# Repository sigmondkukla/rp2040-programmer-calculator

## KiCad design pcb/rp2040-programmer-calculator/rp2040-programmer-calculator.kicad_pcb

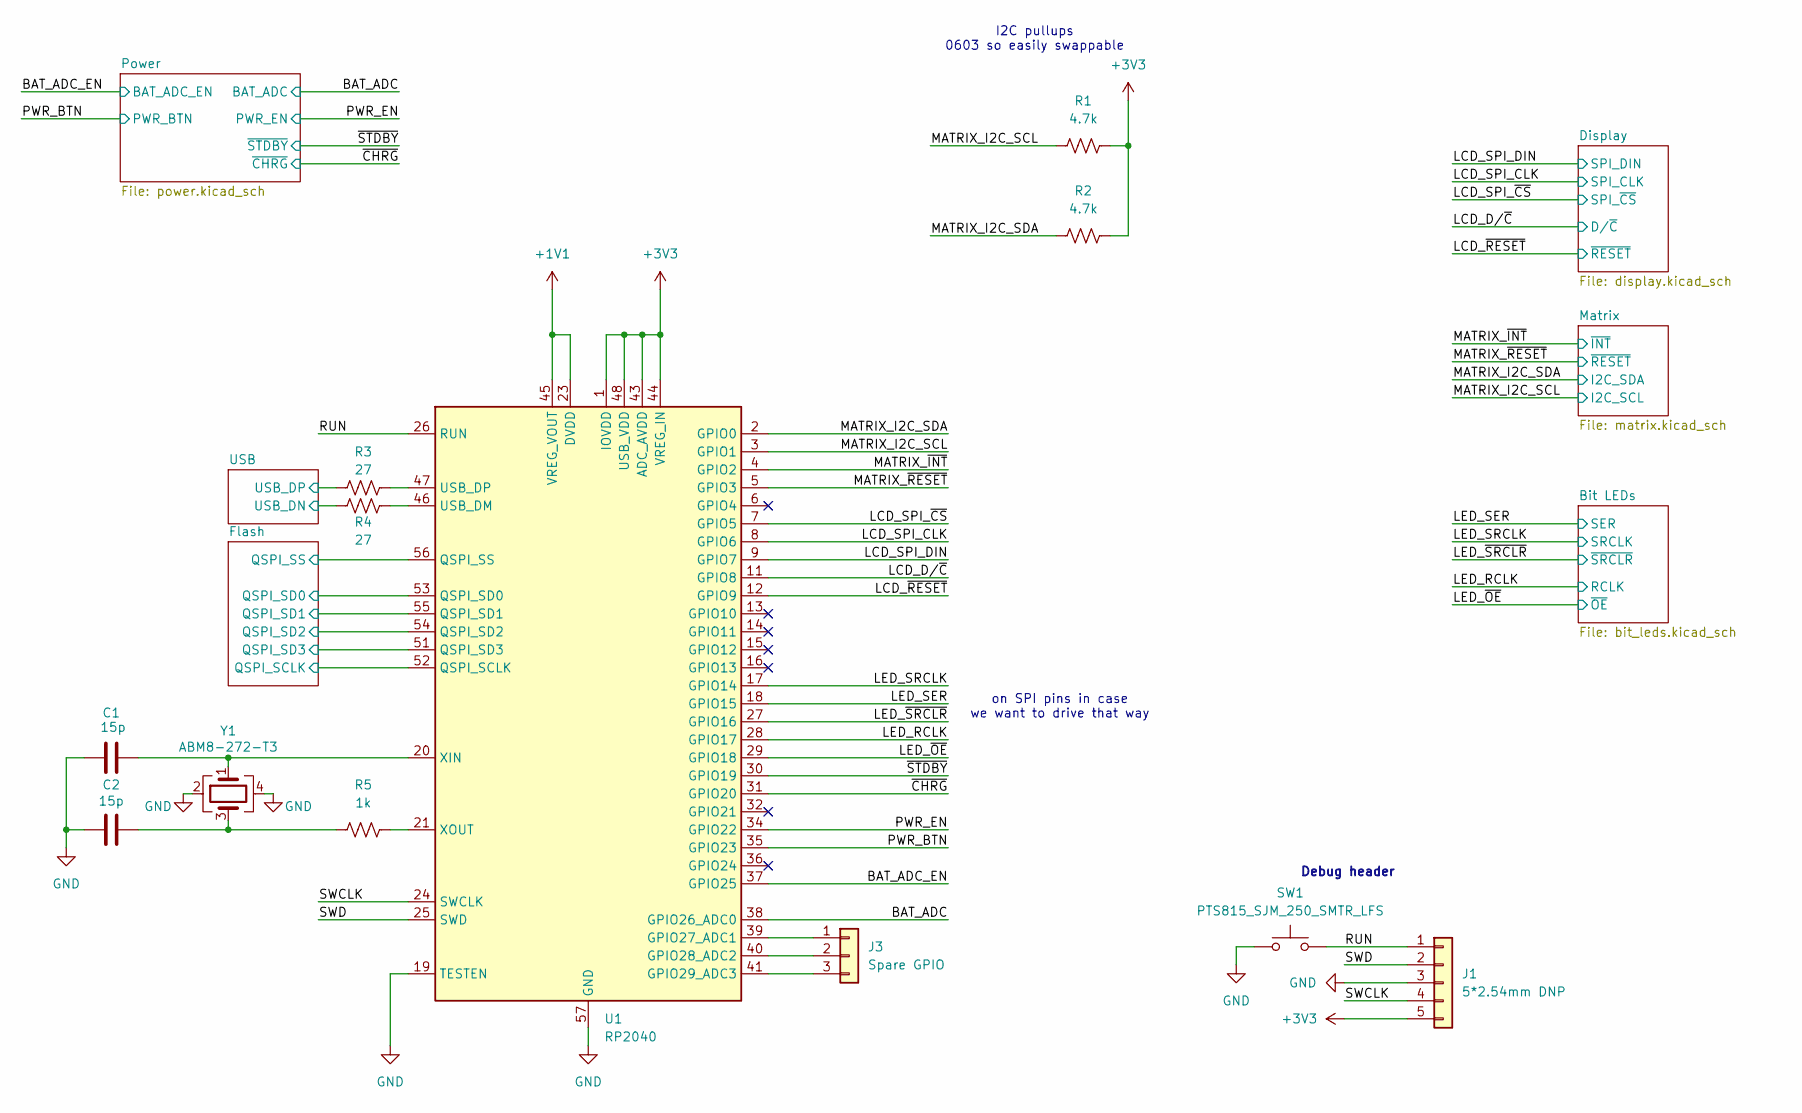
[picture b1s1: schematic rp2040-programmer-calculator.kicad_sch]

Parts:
C1, C2: 15p; C_0402_1005Metric; LCSC C1548
J1: 5*2.54mm DNP; PinHeader_1x05_P2.54mm_Vertical
J3: Spare GPIO; PinHeader_1x03_P2.00mm_Vertical
R1, R2: 4.7k; R_0603_1608Metric
R3, R4: 27; R_0402_1005Metric
R5: 1k; R_0402_1005Metric
SW1: PTS815_SJM_250_SMTR_LFS; SW_Push_PTS815_SJM_250_SMTR_LFS
U1: RP2040; QFN-56-1EP_7x7mm_P0.4mm_EP3.2x3.2mm
Y1: ABM8-272-T3; Crystal_SMD_Abracon_ABM8G-4Pin_3.2x2.5mm; LCSC C20625731

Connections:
+1V1: U1.23 (DVDD), U1.45 (VREG_VOUT), U1.50 (DVDD); also elsewhere on the board
+3V3: J1.5, R1.2, R2.2, U1.1 (IOVDD), U1.10 (IOVDD), U1.22 (IOVDD), U1.33 (IOVDD), U1.42 (IOVDD), U1.43 (ADC_AVDD), U1.44 (VREG_IN), U1.48 (USB_VDD), U1.49 (IOVDD); also elsewhere on the board
/BAT_ADC: U1.38 (GPIO26_ADC0); also elsewhere on the board
/BAT_ADC_EN: U1.37 (GPIO25); also elsewhere on the board
/Flash/QSPI_SCLK: U1.52 (QSPI_SCLK); also elsewhere on the board
/Flash/QSPI_SD0: U1.53 (QSPI_SD0); also elsewhere on the board
/Flash/QSPI_SD1: U1.55 (QSPI_SD1); also elsewhere on the board
/Flash/QSPI_SD2: U1.54 (QSPI_SD2); also elsewhere on the board
/Flash/QSPI_SD3: U1.51 (QSPI_SD3); also elsewhere on the board
/Flash/QSPI_SS: U1.56 (QSPI_SS); also elsewhere on the board
/LCD_D/~C: U1.11 (GPIO8); also elsewhere on the board
/LCD_SPI_CLK: U1.8 (GPIO6); also elsewhere on the board
/LCD_SPI_DIN: U1.9 (GPIO7); also elsewhere on the board
/LCD_SPI_~CS: U1.7 (GPIO5); also elsewhere on the board
/LCD_~RESET: U1.12 (GPIO9); also elsewhere on the board
/LED_RCLK: U1.28 (GPIO17); also elsewhere on the board
/LED_SER: U1.18 (GPIO15); also elsewhere on the board
/LED_SRCLK: U1.17 (GPIO14); also elsewhere on the board
/LED_~OE: U1.29 (GPIO18); also elsewhere on the board
/LED_~SRCLR: U1.27 (GPIO16); also elsewhere on the board
/MATRIX_I2C_SCL: R1.1, U1.3 (GPIO1); also elsewhere on the board
/MATRIX_I2C_SDA: R2.1, U1.2 (GPIO0); also elsewhere on the board
/MATRIX_~INT: U1.4 (GPIO2); also elsewhere on the board
/MATRIX_~RESET: U1.5 (GPIO3); also elsewhere on the board
/PWR_BTN: U1.35 (GPIO23); also elsewhere on the board
/PWR_EN: U1.34 (GPIO22); also elsewhere on the board
/RUN: J1.1, SW1.2, U1.26 (RUN)
/SWCLK: J1.4, U1.24 (SWCLK)
/SWD: J1.2, U1.25 (SWD)
/USB/USB_DN: R4.1; also elsewhere on the board
/USB/USB_DP: R3.1; also elsewhere on the board
/~CHRG: U1.31 (GPIO20); also elsewhere on the board
/~STDBY: U1.30 (GPIO19); also elsewhere on the board
GND: C1.1, C2.1, J1.3, SW1.1, U1.19 (TESTEN), U1.57 (GND), Y1.2, Y1.4; also elsewhere on the board
unnamed: C2.2, R5.1, Y1.3
unnamed: J3.1, U1.39 (GPIO27_ADC1)
unnamed: J3.2, U1.40 (GPIO28_ADC2)
unnamed: J3.3, U1.41 (GPIO29_ADC3)
unnamed: R4.2, U1.46 (USB_DM)
unnamed: R3.2, U1.47 (USB_DP)
unnamed: C1.2, U1.20 (XIN), Y1.1
unnamed: R5.2, U1.21 (XOUT)

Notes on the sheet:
I2C pullups 0603 so easily swappable
on SPI pins in case we want to drive that way
Debug header

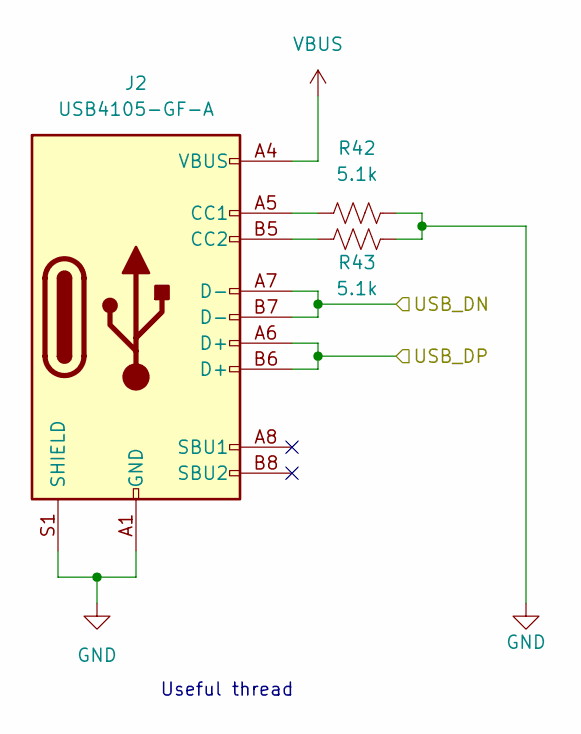
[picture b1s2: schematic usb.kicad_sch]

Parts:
J2: USB4105-GF-A; USB_C_Receptacle_GCT_USB4105-xx-A_16P_TopMnt_Horizontal
R42, R43: 5.1k; R_0603_1608Metric

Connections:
/USB/USB_DN: J2.A7 (D-), J2.B7 (D-); also elsewhere on the board
/USB/USB_DP: J2.A6 (D+), J2.B6 (D+); also elsewhere on the board
GND: J2.A1 (GND), J2.A12 (GND), J2.B1 (GND), J2.B12 (GND), J2.S1 (SHIELD), R42.2, R43.2; also elsewhere on the board
unnamed: J2.A5 (CC1), R42.1
unnamed: J2.B5 (CC2), R43.1
VBUS: J2.A4 (VBUS), J2.A9 (VBUS), J2.B4 (VBUS), J2.B9 (VBUS); also elsewhere on the board

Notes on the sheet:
Useful thread

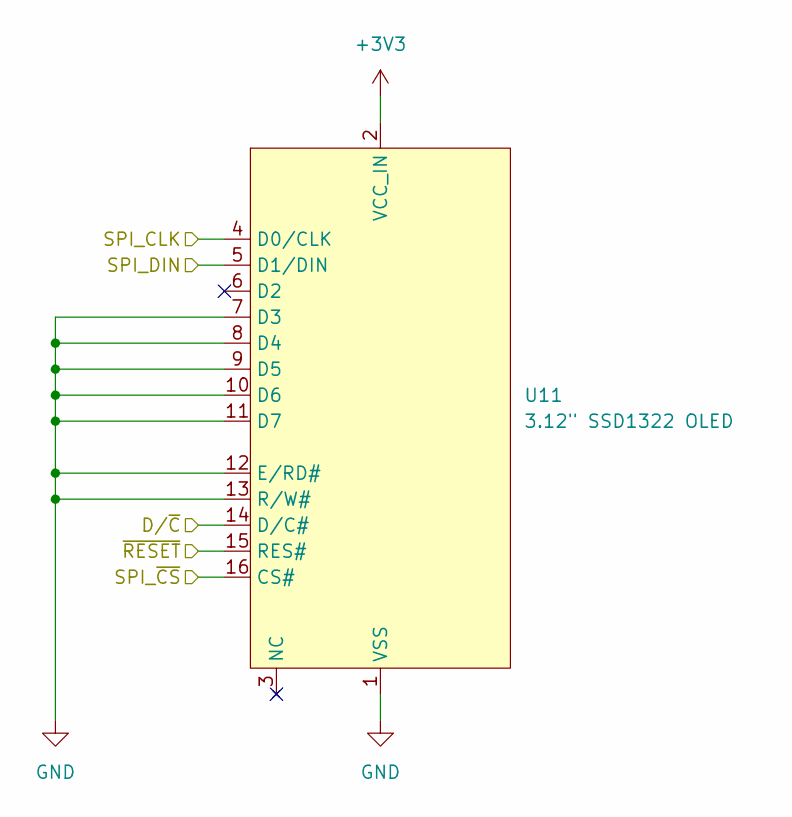
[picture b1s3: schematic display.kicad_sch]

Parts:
U11: 3.12" SSD1322 OLED; SSD1322_OLED

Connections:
+3V3: U11.2 (VCC_IN); also elsewhere on the board
/LCD_D/~C: U11.14 (D/C#); also elsewhere on the board
/LCD_SPI_CLK: U11.4 (D0/CLK); also elsewhere on the board
/LCD_SPI_DIN: U11.5 (D1/DIN); also elsewhere on the board
/LCD_SPI_~CS: U11.16 (CS#); also elsewhere on the board
/LCD_~RESET: U11.15 (RES#); also elsewhere on the board
GND: U11.1 (VSS), U11.7 (D3), U11.8 (D4), U11.9 (D5), U11.10 (D6), U11.11 (D7), U11.12 (E/RD#), U11.13 (R/W#); also elsewhere on the board

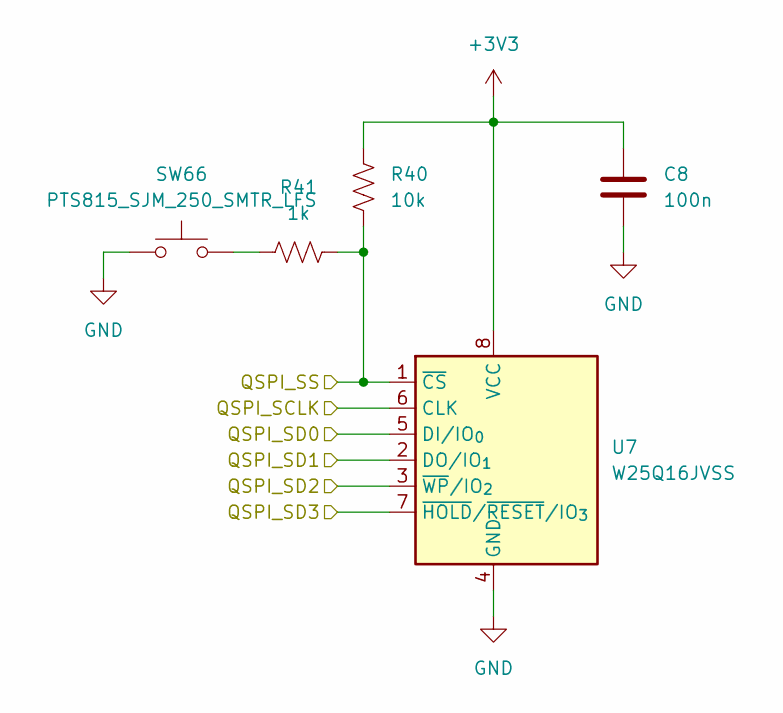
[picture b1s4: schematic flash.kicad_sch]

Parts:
C8: 100n; C_0603_1608Metric
R40: 10k; R_0603_1608Metric
R41: 1k; R_0603_1608Metric
SW66: PTS815_SJM_250_SMTR_LFS; SW_Push_PTS815_SJM_250_SMTR_LFS
U7: W25Q16JVSS; SOIC-8_5.3x5.3mm_P1.27mm

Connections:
+3V3: C8.1, R40.1, U7.8 (VCC); also elsewhere on the board
/Flash/QSPI_SCLK: U7.6 (CLK); also elsewhere on the board
/Flash/QSPI_SD0: U7.5 (DI/IO_{0}); also elsewhere on the board
/Flash/QSPI_SD1: U7.2 (DO/IO_{1}); also elsewhere on the board
/Flash/QSPI_SD2: U7.3 (~WP/IO_{2}); also elsewhere on the board
/Flash/QSPI_SD3: U7.7 (~HOLD/~RESET/IO_{3}); also elsewhere on the board
/Flash/QSPI_SS: R40.2, R41.2, U7.1 (~CS); also elsewhere on the board
GND: C8.2, SW66.1, U7.4 (GND); also elsewhere on the board
unnamed: R41.1, SW66.2

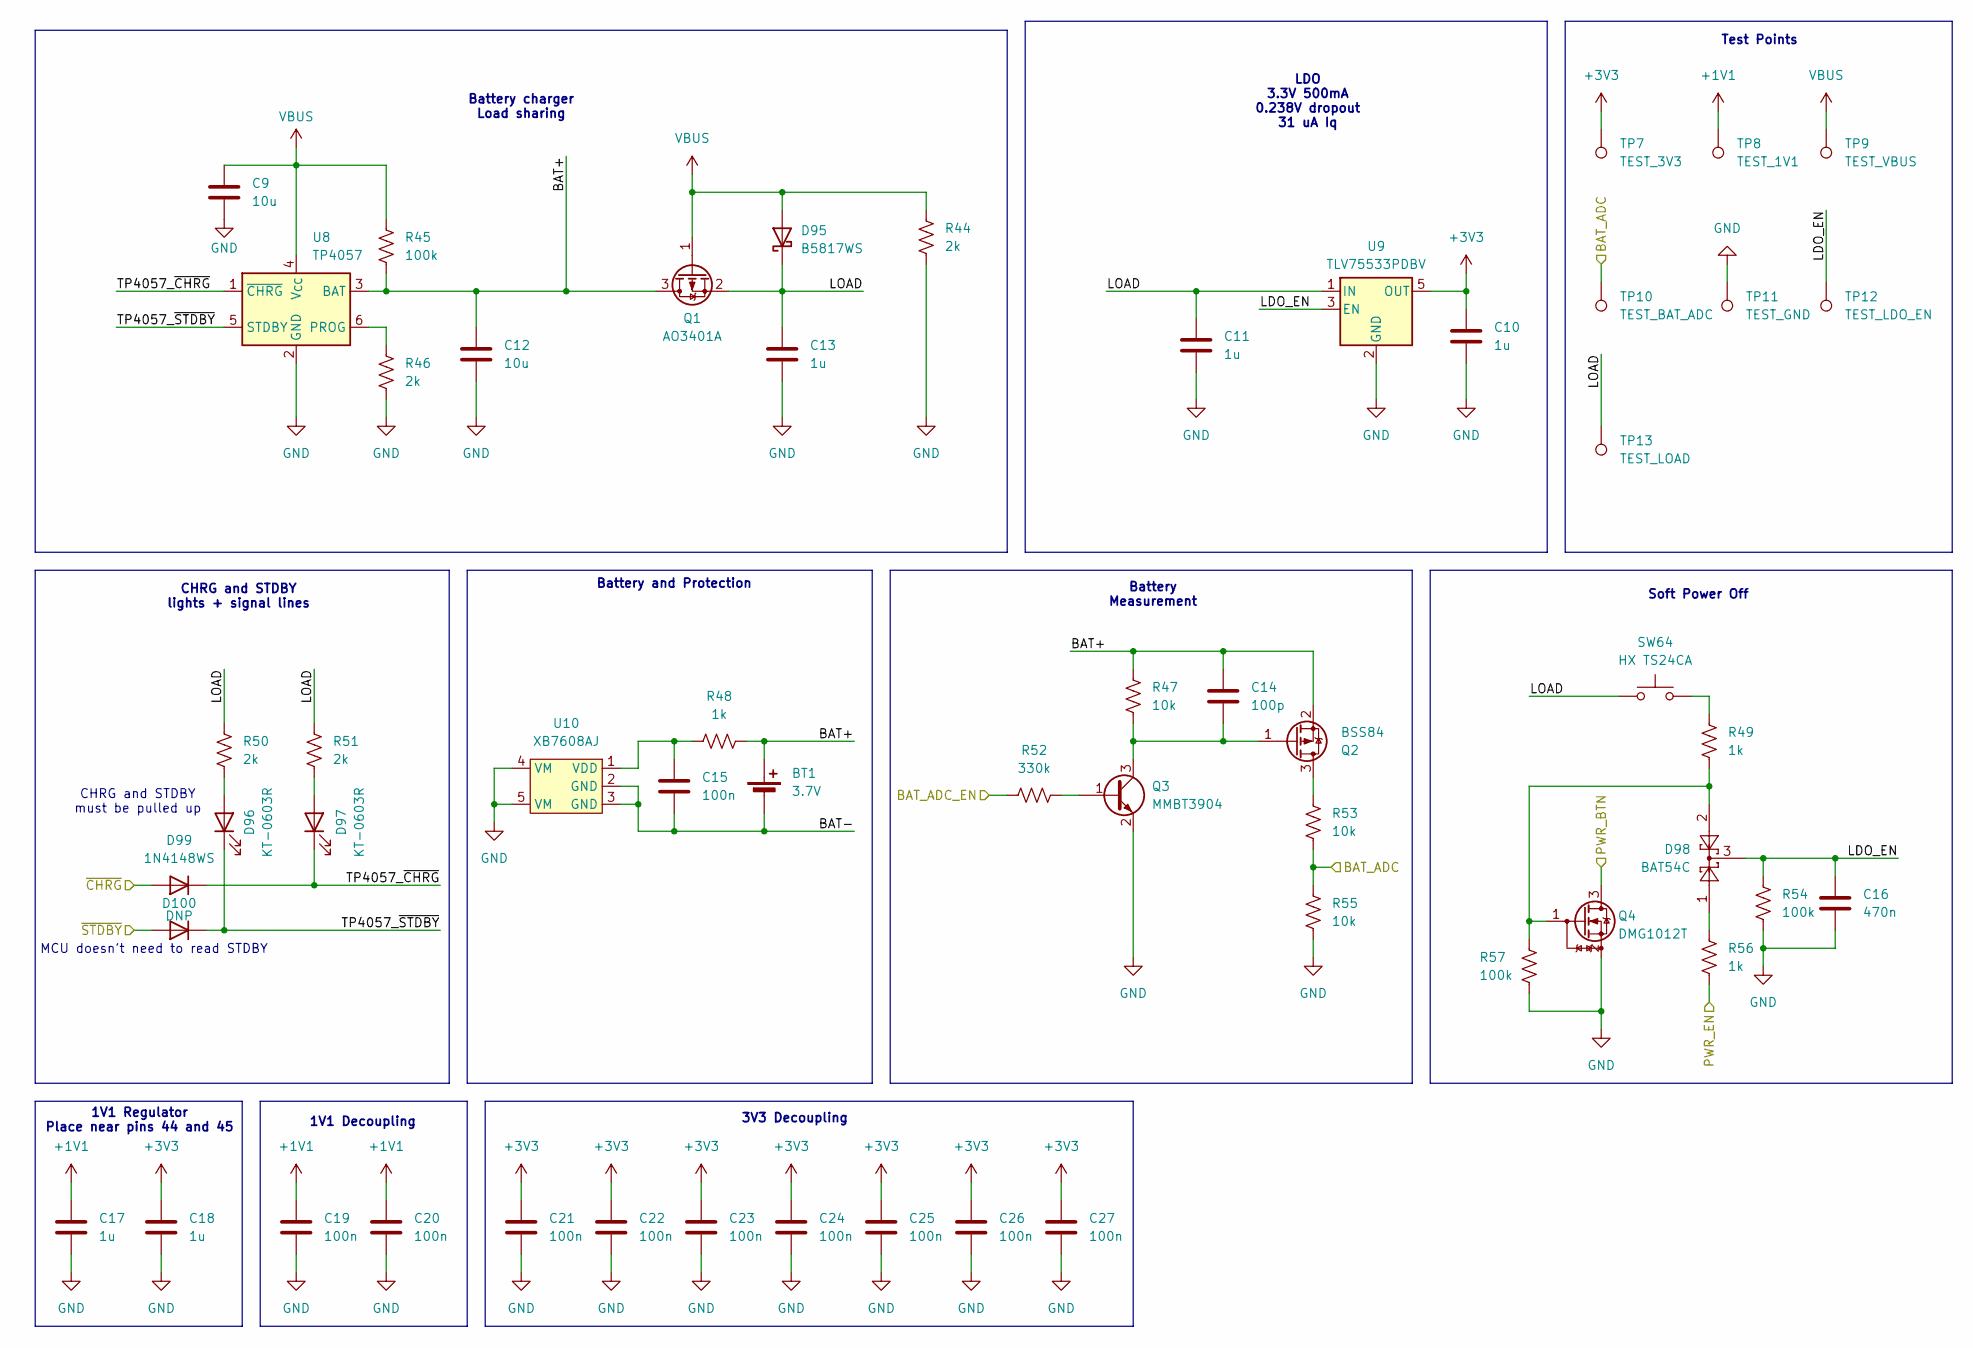
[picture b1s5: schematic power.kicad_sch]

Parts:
BT1: 3.7V; JST_PH_S2B-PH-K_1x02_P2.00mm_Horizontal
C9, C12: 10u; C_0603_1608Metric
C10, C11: 1u; C_0603_1608Metric; LCSC C52923
C13: 1u; C_0603_1608Metric
C14: 100p; C_0603_1608Metric
C15: 100n; C_0603_1608Metric
C16: 470n; C_0603_1608Metric
C17, C18: 1u; C_0402_1005Metric; LCSC C52923
C19, C20, C21, C22, C23, C24, C25, C26, C27: 100n; C_0402_1005Metric; LCSC C1525
D95: B5817WS; D_SOD-323
D96, D97: KT-0603R; LED_0603_1608Metric
D98: BAT54C; SOT-23-3
D99: 1N4148WS; D_SOD-323
D100: DNP; D_SOD-323
Q1: AO3401A; SOT-23-3
Q2: BSS84; SOT-23-3
Q3: MMBT3904; SOT-23
Q4: DMG1012T; SOT-523
R44, R46, R50, R51: 2k; R_0603_1608Metric
R45, R54, R57: 100k; R_0603_1608Metric
R47, R53, R55: 10k; R_0603_1608Metric
R48, R49, R56: 1k; R_0603_1608Metric
R52: 330k; R_0603_1608Metric
SW64: HX TS24CA; HX-TS24CA
TP7: TEST_3V3; TestPoint_Pad_D1.0mm
TP8: TEST_1V1; TestPoint_Pad_D1.0mm
TP9: TEST_VBUS; TestPoint_Pad_D1.0mm
TP10: TEST_BAT_ADC; TestPoint_Pad_D1.0mm
TP11: TEST_GND; TestPoint_Pad_D1.0mm
TP12: TEST_LDO_EN; TestPoint_Pad_D1.0mm
TP13: TEST_LOAD; TestPoint_Pad_D1.0mm
U8: TP4057; TSOT-23-6
U9: TLV75533PDBV; SOT-23-5
U10: XB7608AJ; CPC-5_L2.6-W2.6-P0.53-LS4.0-BL

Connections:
+1V1: C17.1, C19.1, C20.1, TP8.1; also elsewhere on the board
+3V3: C10.1, C18.1, C21.1, C22.1, C23.1, C24.1, C25.1, C26.1, C27.1, TP7.1, U9.5 (OUT); also elsewhere on the board
/BAT_ADC: R53.1, R55.2, TP10.1; also elsewhere on the board
/BAT_ADC_EN: R52.1; also elsewhere on the board
/PWR_BTN: Q4.3 (D); also elsewhere on the board
/PWR_EN: R56.2; also elsewhere on the board
/Power/BAT+: BT1.1 (+), C12.1, C14.1, Q1.3 (D), Q2.2 (S), R45.2, R47.2, R48.2, U8.3 (BAT)
/Power/BAT-: BT1.2 (-), C15.2, U10.2 (GND), U10.3 (GND)
/Power/LDO_EN: C16.1, D98.3, R54.1, TP12.1, U9.3 (EN)
/Power/LOAD: C11.1, C13.1, D95.1 (K), Q1.2 (S), R50.1, R51.1, SW64.2, TP13.1, U9.1 (IN)
/Power/TP4057_~CHRG: D97.1 (K), D99.1 (K), U8.1 (~CHRG)
/Power/TP4057_~STDBY: D96.1 (K), D100.1 (K), U8.5 (STDBY)
/~CHRG: D99.2 (A); also elsewhere on the board
/~STDBY: D100.2 (A); also elsewhere on the board
GND: C9.2, C10.2, C11.2, C12.2, C13.2, C16.2, C17.2, C18.2, C19.2, C20.2, C21.2, C22.2, C23.2, C24.2, C25.2, C26.2, C27.2, Q3.2 (E), Q4.2 (S), R44.2, R46.2, R54.2, R55.1, R57.2, TP11.1, U8.2 (GND), U9.2 (GND), U10.4 (VM), U10.5 (VM); also elsewhere on the board
unnamed: D96.2 (A), R50.2
unnamed: D97.2 (A), R51.2
unnamed: D98.1, R56.1
unnamed: Q2.3 (D), R53.2
unnamed: C14.2, Q2.1 (G), Q3.3 (C), R47.1
unnamed: Q3.1 (B), R52.2
unnamed: D98.2, Q4.1 (G), R49.2, R57.1
unnamed: R49.1, SW64.1
unnamed: R46.1, U8.6 (PROG)
unnamed: C15.1, R48.1, U10.1 (VDD)
VBUS: C9.1, D95.2 (A), Q1.1 (G), R44.1, R45.1, TP9.1, U8.4 (V_{CC}); also elsewhere on the board

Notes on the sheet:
MCU doesn't need to read STDBY
Battery Measurement
CHRG and STDBY lights + signal lines
CHRG and STDBY must be pulled up
LDO 3.3V 500mA 0.238V dropout 31 uA Iq
Test Points
3V3 Decoupling
Battery charger Load sharing
Soft Power Off
Battery and Protection
1V1 Regulator Place near pins 44 and 45
1V1 Decoupling

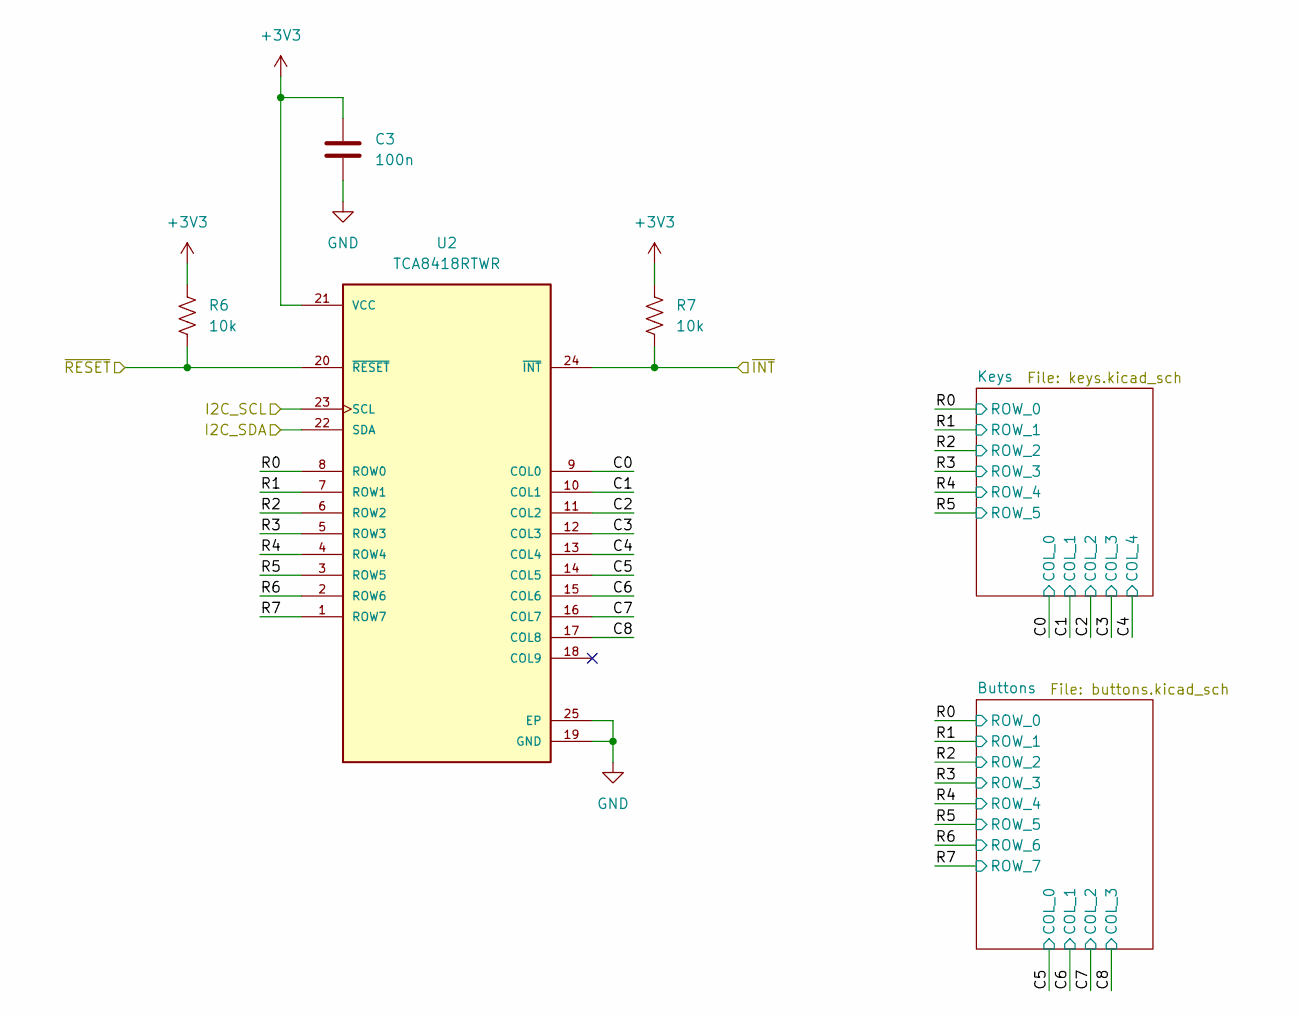
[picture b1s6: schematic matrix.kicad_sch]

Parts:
C3: 100n; C_0603_1608Metric
R6, R7: 10k; R_0603_1608Metric
U2: TCA8418RTWR; QFN50P400X400X80-25N; PARTREV G

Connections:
+3V3: C3.1, R6.1, R7.1, U2.21 (VCC); also elsewhere on the board
/MATRIX_I2C_SCL: U2.23 (SCL); also elsewhere on the board
/MATRIX_I2C_SDA: U2.22 (SDA); also elsewhere on the board
/MATRIX_~INT: R7.2, U2.24 (~INT); also elsewhere on the board
/MATRIX_~RESET: R6.2, U2.20 (~RESET); also elsewhere on the board
/Matrix/C0: U2.9 (COL0); also elsewhere on the board
/Matrix/C1: U2.10 (COL1); also elsewhere on the board
/Matrix/C2: U2.11 (COL2); also elsewhere on the board
/Matrix/C3: U2.12 (COL3); also elsewhere on the board
/Matrix/C4: U2.13 (COL4); also elsewhere on the board
/Matrix/C5: U2.14 (COL5); also elsewhere on the board
/Matrix/C6: U2.15 (COL6); also elsewhere on the board
/Matrix/C7: U2.16 (COL7); also elsewhere on the board
/Matrix/C8: U2.17 (COL8); also elsewhere on the board
/Matrix/R0: U2.8 (ROW0); also elsewhere on the board
/Matrix/R1: U2.7 (ROW1); also elsewhere on the board
/Matrix/R2: U2.6 (ROW2); also elsewhere on the board
/Matrix/R3: U2.5 (ROW3); also elsewhere on the board
/Matrix/R4: U2.4 (ROW4); also elsewhere on the board
/Matrix/R5: U2.3 (ROW5); also elsewhere on the board
/Matrix/R6: U2.2 (ROW6); also elsewhere on the board
/Matrix/R7: U2.1 (ROW7); also elsewhere on the board
GND: C3.2, U2.19 (GND), U2.25 (EP); also elsewhere on the board

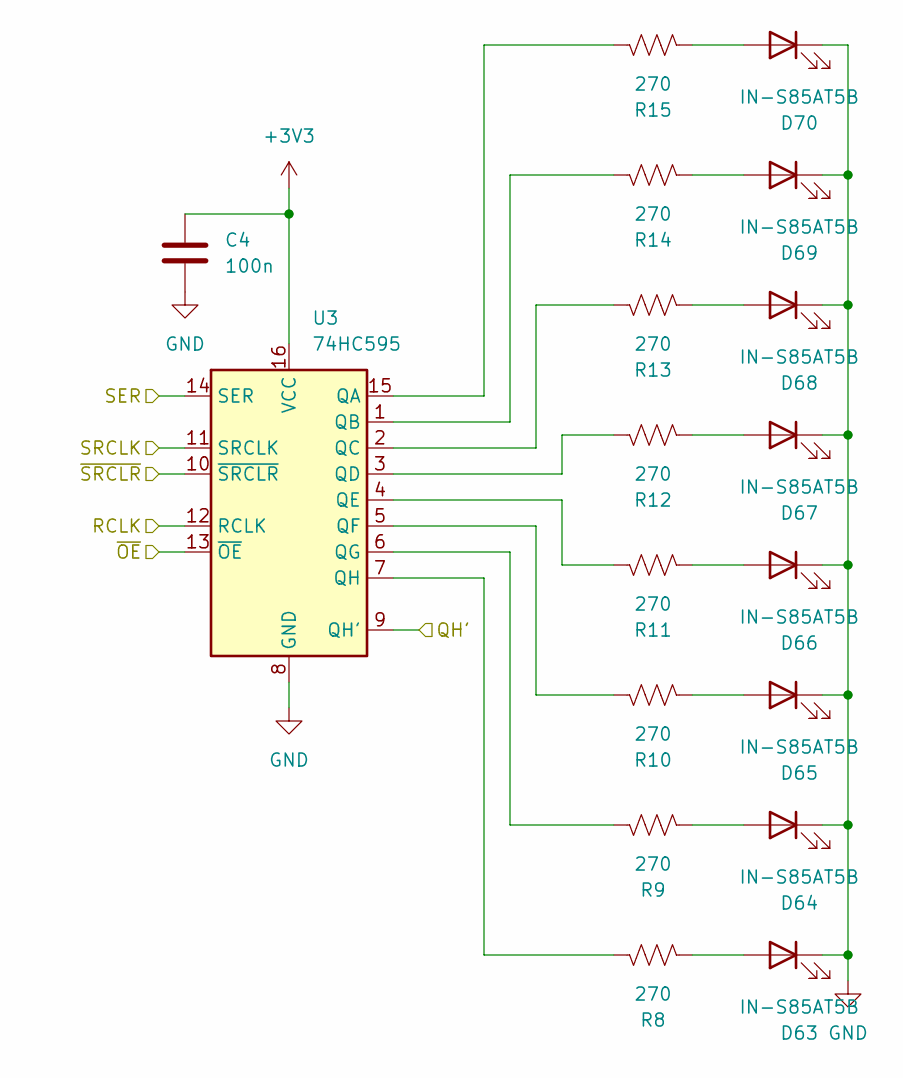
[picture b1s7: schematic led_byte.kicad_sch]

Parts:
C4: 100n; C_0603_1608Metric
D63, D64, D65, D66, D67, D68, D69, D70: IN-S85AT5B; LED_0805_2012Metric_Pad1.15x1.40mm_HandSolder
R8, R9, R10, R11, R12, R13, R14, R15: 270; R_0603_1608Metric_Pad0.98x0.95mm_HandSolder
U3: 74HC595; SOIC-16_3.9x9.9mm_P1.27mm

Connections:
+3V3: C4.1, U3.16 (VCC); also elsewhere on the board
/Bit LEDs/BYTE_0_OUT: U3.9 (QH'); also elsewhere on the board
/LED_RCLK: U3.12 (RCLK); also elsewhere on the board
/LED_SER: U3.14 (SER); also elsewhere on the board
/LED_SRCLK: U3.11 (SRCLK); also elsewhere on the board
/LED_~OE: U3.13 (~OE); also elsewhere on the board
/LED_~SRCLR: U3.10 (~SRCLR); also elsewhere on the board
GND: C4.2, D63.1 (K), D64.1 (K), D65.1 (K), D66.1 (K), D67.1 (K), D68.1 (K), D69.1 (K), D70.1 (K), U3.8 (GND); also elsewhere on the board
unnamed: D63.2 (A), R8.2
unnamed: D64.2 (A), R9.2
unnamed: D65.2 (A), R10.2
unnamed: D66.2 (A), R11.2
unnamed: D67.2 (A), R12.2
unnamed: D68.2 (A), R13.2
unnamed: D69.2 (A), R14.2
unnamed: D70.2 (A), R15.2
unnamed: R15.1, U3.15 (QA)
unnamed: R14.1, U3.1 (QB)
unnamed: R13.1, U3.2 (QC)
unnamed: R12.1, U3.3 (QD)
unnamed: R11.1, U3.4 (QE)
unnamed: R10.1, U3.5 (QF)
unnamed: R9.1, U3.6 (QG)
unnamed: R8.1, U3.7 (QH)

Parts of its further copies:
C5, C6, C7: 100n; C_0603_1608Metric
D71, D72, D73, D74, D75, D76, D77, D78, D79, D80, D81, D82, D83, D84, D85, D86, D87, D88, D89, D90, D91, D92, D93, D94: IN-S85AT5B; LED_0805_2012Metric_Pad1.15x1.40mm_HandSolder
R16, R17, R18, R19, R20, R21, R22, R23, R24, R25, R26, R27, R28, R29, R30, R31, R32, R33, R34, R35, R36, R37, R38, R39: 270; R_0603_1608Metric_Pad0.98x0.95mm_HandSolder
U4, U5, U6: 74HC595; SOIC-16_3.9x9.9mm_P1.27mm

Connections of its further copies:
+3V3: C5.1, C6.1, C7.1, U4.16 (VCC), U5.16 (VCC), U6.16 (VCC); also elsewhere on the board
/Bit LEDs/BYTE_0_OUT: U4.14 (SER); also elsewhere on the board
/Bit LEDs/BYTE_1_OUT: U4.9 (QH'), U5.14 (SER)
/Bit LEDs/BYTE_2_OUT: U5.9 (QH'), U6.14 (SER)
/Bit LEDs/LED_Byte_3/QH&apos;: U6.9 (QH')
/LED_RCLK: U4.12 (RCLK), U5.12 (RCLK), U6.12 (RCLK); also elsewhere on the board
/LED_SRCLK: U4.11 (SRCLK), U5.11 (SRCLK), U6.11 (SRCLK); also elsewhere on the board
/LED_~OE: U4.13 (~OE), U5.13 (~OE), U6.13 (~OE); also elsewhere on the board
/LED_~SRCLR: U4.10 (~SRCLR), U5.10 (~SRCLR), U6.10 (~SRCLR); also elsewhere on the board
GND: C5.2, C6.2, C7.2, D71.1 (K), D72.1 (K), D73.1 (K), D74.1 (K), D75.1 (K), D76.1 (K), D77.1 (K), D78.1 (K), D79.1 (K), D80.1 (K), D81.1 (K), D82.1 (K), D83.1 (K), D84.1 (K), D85.1 (K), D86.1 (K), D87.1 (K), D88.1 (K), D89.1 (K), D90.1 (K), D91.1 (K), D92.1 (K), D93.1 (K), D94.1 (K), U4.8 (GND), U5.8 (GND), U6.8 (GND); also elsewhere on the board
unnamed: D71.2 (A), R16.2
unnamed: D72.2 (A), R17.2
unnamed: D73.2 (A), R18.2
unnamed: D74.2 (A), R19.2
unnamed: D75.2 (A), R20.2
unnamed: D76.2 (A), R21.2
unnamed: D77.2 (A), R22.2
unnamed: D78.2 (A), R23.2
unnamed: D79.2 (A), R24.2
unnamed: D80.2 (A), R25.2
unnamed: D81.2 (A), R26.2
unnamed: D82.2 (A), R27.2
unnamed: D83.2 (A), R28.2
unnamed: D84.2 (A), R29.2
unnamed: D85.2 (A), R30.2
unnamed: D86.2 (A), R31.2
unnamed: D87.2 (A), R32.2
unnamed: D88.2 (A), R33.2
unnamed: D89.2 (A), R34.2
unnamed: D90.2 (A), R35.2
unnamed: D91.2 (A), R36.2
unnamed: D92.2 (A), R37.2
unnamed: D93.2 (A), R38.2
unnamed: D94.2 (A), R39.2
unnamed: R23.1, U4.15 (QA)
unnamed: R22.1, U4.1 (QB)
unnamed: R21.1, U4.2 (QC)
unnamed: R20.1, U4.3 (QD)
unnamed: R19.1, U4.4 (QE)
unnamed: R18.1, U4.5 (QF)
unnamed: R17.1, U4.6 (QG)
unnamed: R16.1, U4.7 (QH)
unnamed: R31.1, U5.15 (QA)
unnamed: R30.1, U5.1 (QB)
unnamed: R29.1, U5.2 (QC)
unnamed: R28.1, U5.3 (QD)
unnamed: R27.1, U5.4 (QE)
unnamed: R26.1, U5.5 (QF)
unnamed: R25.1, U5.6 (QG)
unnamed: R24.1, U5.7 (QH)
unnamed: R39.1, U6.15 (QA)
unnamed: R38.1, U6.1 (QB)
unnamed: R37.1, U6.2 (QC)
unnamed: R36.1, U6.3 (QD)
unnamed: R35.1, U6.4 (QE)
unnamed: R34.1, U6.5 (QF)
unnamed: R33.1, U6.6 (QG)
unnamed: R32.1, U6.7 (QH)

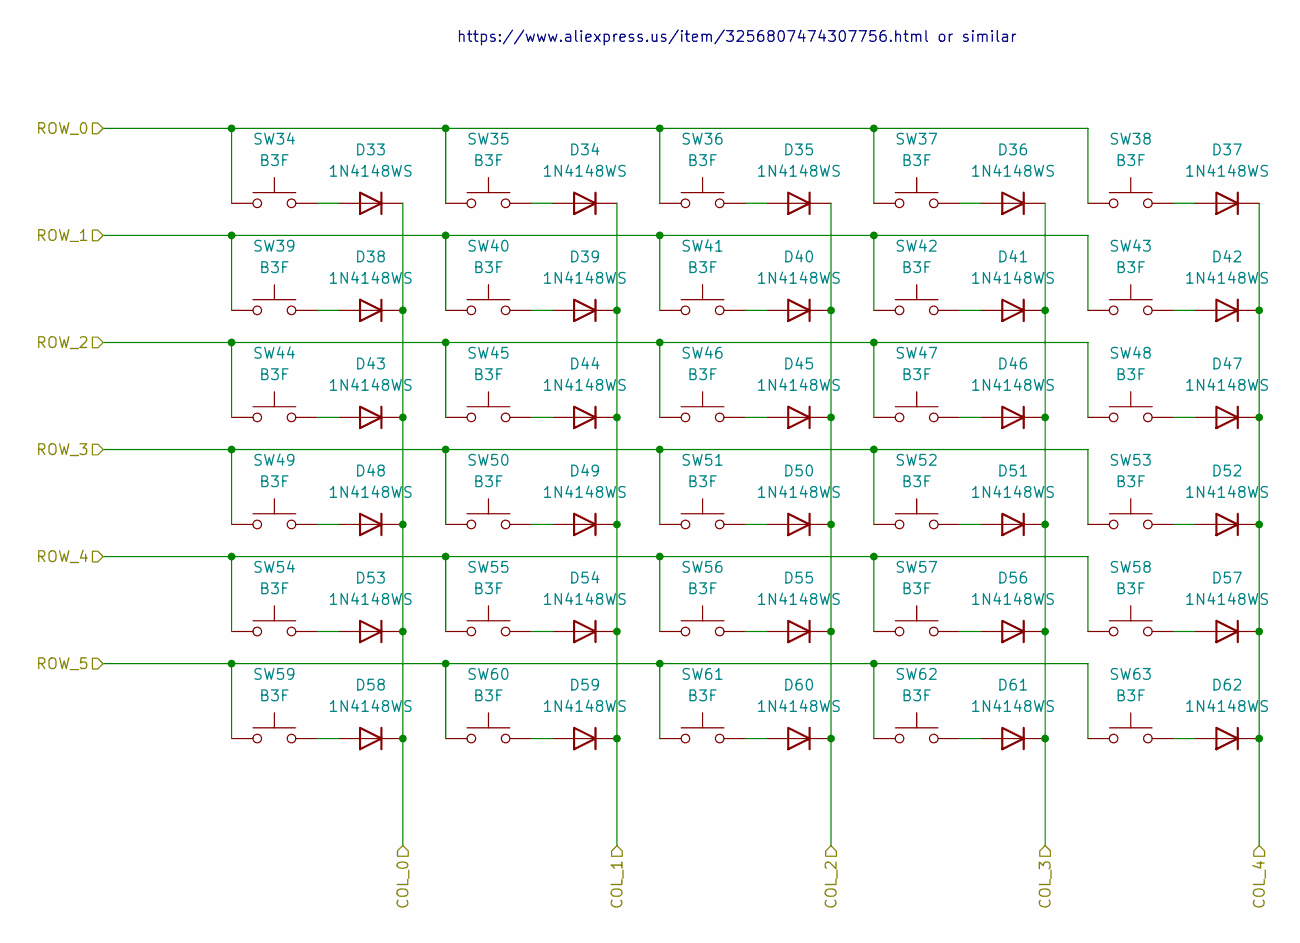
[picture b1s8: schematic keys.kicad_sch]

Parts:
D33, D34, D35, D36, D37, D38, D39, D40, D41, D42, D43, D44, D45, D46, D47, D48, D49, D50, D51, D52, D53, D54, D55, D56, D57, D58, D59, D60, D61, D62: 1N4148WS; D_SOD-323
SW34, SW35, SW36, SW37, SW38, SW39, SW40, SW41, SW42, SW43, SW44, SW45, SW46, SW47, SW48, SW49, SW50, SW51, SW52, SW53, SW54, SW55, SW56, SW57, SW58, SW59, SW60, SW61, SW62, SW63: B3F; SW_SPST_Omron_B3F-40xx

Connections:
/Matrix/C0: D33.1 (K), D38.1 (K), D43.1 (K), D48.1 (K), D53.1 (K), D58.1 (K); also elsewhere on the board
/Matrix/C1: D34.1 (K), D39.1 (K), D44.1 (K), D49.1 (K), D54.1 (K), D59.1 (K); also elsewhere on the board
/Matrix/C2: D35.1 (K), D40.1 (K), D45.1 (K), D50.1 (K), D55.1 (K), D60.1 (K); also elsewhere on the board
/Matrix/C3: D36.1 (K), D41.1 (K), D46.1 (K), D51.1 (K), D56.1 (K), D61.1 (K); also elsewhere on the board
/Matrix/C4: D37.1 (K), D42.1 (K), D47.1 (K), D52.1 (K), D57.1 (K), D62.1 (K); also elsewhere on the board
/Matrix/R0: SW34.1, SW35.1, SW36.1, SW37.1, SW38.1; also elsewhere on the board
/Matrix/R1: SW39.1, SW40.1, SW41.1, SW42.1, SW43.1; also elsewhere on the board
/Matrix/R2: SW44.1, SW45.1, SW46.1, SW47.1, SW48.1; also elsewhere on the board
/Matrix/R3: SW49.1, SW50.1, SW51.1, SW52.1, SW53.1; also elsewhere on the board
/Matrix/R4: SW54.1, SW55.1, SW56.1, SW57.1, SW58.1; also elsewhere on the board
/Matrix/R5: SW59.1, SW60.1, SW61.1, SW62.1, SW63.1; also elsewhere on the board
unnamed: D33.2 (A), SW34.2
unnamed: D34.2 (A), SW35.2
unnamed: D35.2 (A), SW36.2
unnamed: D36.2 (A), SW37.2
unnamed: D37.2 (A), SW38.2
unnamed: D38.2 (A), SW39.2
unnamed: D39.2 (A), SW40.2
unnamed: D40.2 (A), SW41.2
unnamed: D41.2 (A), SW42.2
unnamed: D42.2 (A), SW43.2
unnamed: D43.2 (A), SW44.2
unnamed: D44.2 (A), SW45.2
unnamed: D45.2 (A), SW46.2
unnamed: D46.2 (A), SW47.2
unnamed: D47.2 (A), SW48.2
unnamed: D48.2 (A), SW49.2
unnamed: D49.2 (A), SW50.2
unnamed: D50.2 (A), SW51.2
unnamed: D51.2 (A), SW52.2
unnamed: D52.2 (A), SW53.2
unnamed: D53.2 (A), SW54.2
unnamed: D54.2 (A), SW55.2
unnamed: D55.2 (A), SW56.2
unnamed: D56.2 (A), SW57.2
unnamed: D57.2 (A), SW58.2
unnamed: D58.2 (A), SW59.2
unnamed: D59.2 (A), SW60.2
unnamed: D60.2 (A), SW61.2
unnamed: D61.2 (A), SW62.2
unnamed: D62.2 (A), SW63.2

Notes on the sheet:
https://www.aliexpress.us/item/3256807474307756.html or similar

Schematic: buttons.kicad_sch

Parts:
D1, D2, D3, D4, D5, D6, D7, D8, D9, D10, D11, D12, D13, D14, D15, D16, D17, D18, D19, D20, D21, D22, D23, D24, D25, D26, D27, D28, D29, D30, D31, D32: 1N4148WS; D_SOD-323
SW2, SW3, SW4, SW5, SW6, SW7, SW8, SW9, SW10, SW11, SW12, SW13, SW14, SW15, SW16, SW17, SW18, SW19, SW20, SW21, SW22, SW23, SW24, SW25, SW26, SW27, SW28, SW29, SW30, SW31, SW32, SW33: PTS636SL50 LFS; PTS636SL50LFS

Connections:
/Matrix/C5: D1.1 (K), D2.1 (K), D3.1 (K), D4.1 (K), D5.1 (K), D6.1 (K), D7.1 (K), D8.1 (K); also elsewhere on the board
/Matrix/C6: D9.1 (K), D10.1 (K), D11.1 (K), D12.1 (K), D13.1 (K), D14.1 (K), D15.1 (K), D16.1 (K); also elsewhere on the board
/Matrix/C7: D17.1 (K), D18.1 (K), D19.1 (K), D20.1 (K), D21.1 (K), D22.1 (K), D23.1 (K), D24.1 (K); also elsewhere on the board
/Matrix/C8: D25.1 (K), D26.1 (K), D27.1 (K), D28.1 (K), D29.1 (K), D30.1 (K), D31.1 (K), D32.1 (K); also elsewhere on the board
/Matrix/R0: SW2.1, SW10.1, SW18.1, SW26.1; also elsewhere on the board
/Matrix/R1: SW3.1, SW11.1, SW19.1, SW27.1; also elsewhere on the board
/Matrix/R2: SW4.1, SW12.1, SW20.1, SW28.1; also elsewhere on the board
/Matrix/R3: SW5.1, SW13.1, SW21.1, SW29.1; also elsewhere on the board
/Matrix/R4: SW6.1, SW14.1, SW22.1, SW30.1; also elsewhere on the board
/Matrix/R5: SW7.1, SW15.1, SW23.1, SW31.1; also elsewhere on the board
/Matrix/R6: SW8.1, SW16.1, SW24.1, SW32.1; also elsewhere on the board
/Matrix/R7: SW9.1, SW17.1, SW25.1, SW33.1; also elsewhere on the board
unnamed: D1.2 (A), SW2.2
unnamed: D2.2 (A), SW3.2
unnamed: D3.2 (A), SW4.2
unnamed: D4.2 (A), SW5.2
unnamed: D5.2 (A), SW6.2
unnamed: D6.2 (A), SW7.2
unnamed: D7.2 (A), SW8.2
unnamed: D8.2 (A), SW9.2
unnamed: D9.2 (A), SW10.2
unnamed: D10.2 (A), SW11.2
unnamed: D11.2 (A), SW12.2
unnamed: D12.2 (A), SW13.2
unnamed: D13.2 (A), SW14.2
unnamed: D14.2 (A), SW15.2
unnamed: D15.2 (A), SW16.2
unnamed: D16.2 (A), SW17.2
unnamed: D17.2 (A), SW18.2
unnamed: D18.2 (A), SW19.2
unnamed: D19.2 (A), SW20.2
unnamed: D20.2 (A), SW21.2
unnamed: D21.2 (A), SW22.2
unnamed: D22.2 (A), SW23.2
unnamed: D23.2 (A), SW24.2
unnamed: D24.2 (A), SW25.2
unnamed: D25.2 (A), SW26.2
unnamed: D26.2 (A), SW27.2
unnamed: D27.2 (A), SW28.2
unnamed: D28.2 (A), SW29.2
unnamed: D29.2 (A), SW30.2
unnamed: D30.2 (A), SW31.2
unnamed: D31.2 (A), SW32.2
unnamed: D32.2 (A), SW33.2

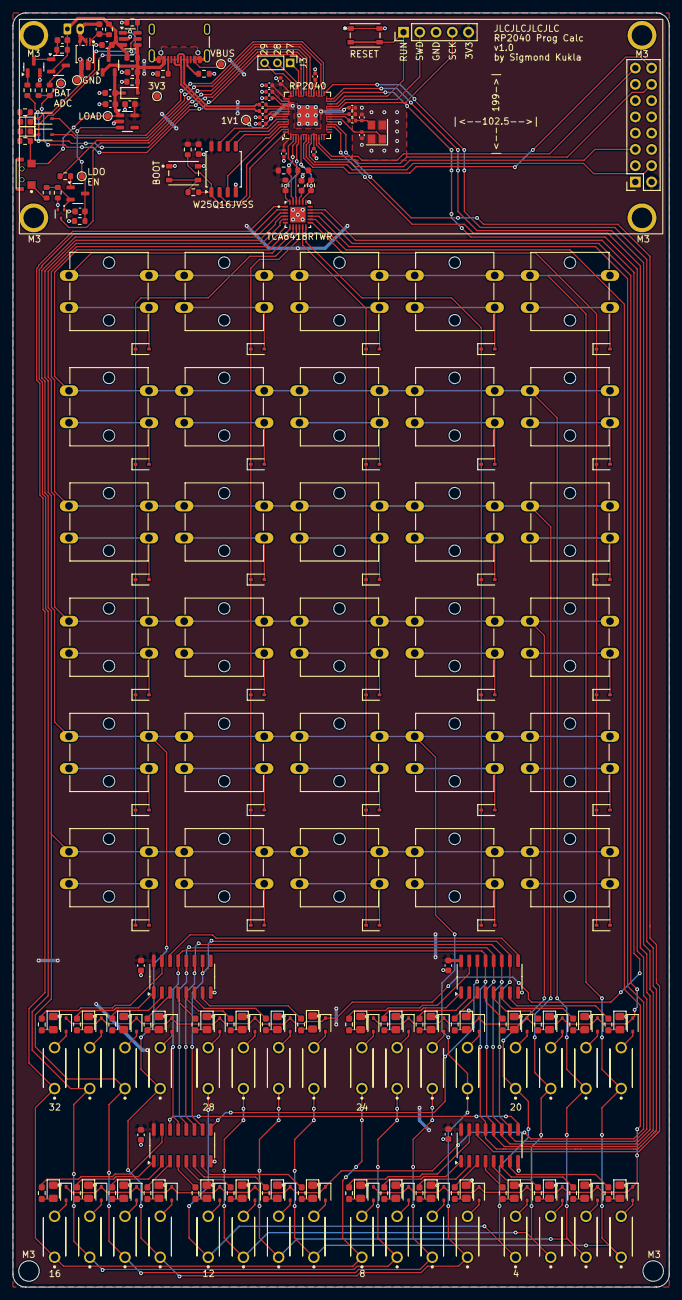
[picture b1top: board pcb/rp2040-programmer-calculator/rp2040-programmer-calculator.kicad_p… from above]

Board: 2 copper layers, 102.5 x 199.0 mm, 276 parts (1 on the bottom side), 208 nets.
